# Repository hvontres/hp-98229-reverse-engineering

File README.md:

# hp 98229 Memory Module reverse engineering
This is an attempt at documenting the HP 98229 Memory module used in the HP 9000 375/380/385 models.

It comes in 2mb, 4mb 8mb and 16mb sizes. The 4mb size seems to exist in two flavors: the older version using 36 256K x 4 memory chips and a newer version using 9 1M x 4 chips.

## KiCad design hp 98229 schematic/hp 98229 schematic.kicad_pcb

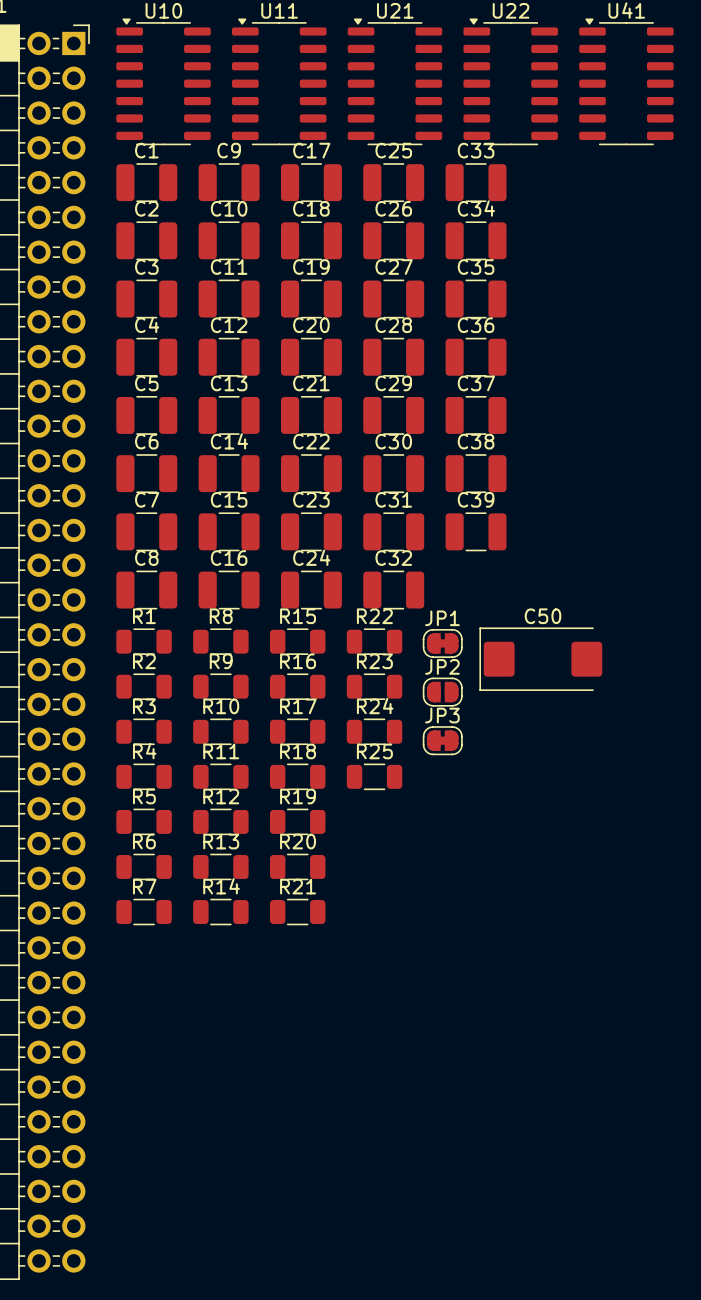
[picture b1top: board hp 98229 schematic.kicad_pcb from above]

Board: 2 copper layers, 74 parts (0 on the bottom side), 51 nets, no tracks yet.

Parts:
C1, C2, C3, C4, C5, C6, C7, C8, C9, C10, C11, C12, C13, C14, C15, C16, C17, C18, C19, C20, C21, C22, C23, C24, C25, C26, C27, C28, C29, C30, C31, C32, C33, C34, C35, C36, C37, C38, C39: 0.1 uF; C_1210_3225Metric_Pad1.33x2.70mm_HandSolder
C50: 47 uF; CP_EIA-7343-20_Kemet-V_Pad2.25x2.55mm_HandSolder
J1: Conn_02x36_Top_Bottom; PinSocket_2x36_P2.54mm_Horizontal
JP1: Jumper_2_Bridged; SolderJumper-2_P1.3mm_Bridged_RoundedPad1.0x1.5mm
JP2: Jumper_2_Open; SolderJumper-2_P1.3mm_Open_RoundedPad1.0x1.5mm
JP3: Jumper_2_closed; SolderJumper-2_P1.3mm_Bridged_RoundedPad1.0x1.5mm
R1, R2, R3, R4, R5, R6, R7, R8, R9, R10, R11, R12, R13, R14, R15, R16, R17, R18, R19, R20, R21, R22, R23, R24, R25: 15; R_1206_3216Metric
U10, U11, U21, U22, U41: 74AHCT04; SOIC-14_3.9x8.7mm_P1.27mm

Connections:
/CAS0: J1.18, U10.9
/CAS1: J1.55, U21.9
/CAS2: J1.15, U41.1
/CAS3: J1.50, U41.3
/ID0: J1.24, JP1.2 (B)
/ID1: J1.23, JP2.1 (A)
/ID2: J1.61, JP3.2 (B)
/OE: J1.17, U21.13, U41.5
/RAS: J1.53, U11.5, U22.5, U41.9, U41.13
/WRITE0: J1.52, U11.11
/WRITE1: J1.20, U21.5
/WRITE2: J1.56, U11.9
/WRITE3: J1.14, U21.11
/WRITE4: J1.49, U21.1
/~A0: J1.22, U10.5
/~A1: J1.60, U22.9
/~A2: J1.21, U22.13
/~A3: J1.59, U22.11
/~A4: J1.12, U11.1
/~A5: J1.58, U11.13
/~A6: J1.11, U10.13
/~A7: J1.48, U10.1
/~A8: J1.10, U22.1
/~A9: J1.47, U10.3
GND: C1.1, C2.1, C3.1, C4.1, C5.1, C6.1, C7.1, C8.1, C9.1, C10.1, C11.1, C12.1, C13.1, C14.1, C15.1, C16.1, C17.1, C18.1, C19.1, C20.1, C21.1, C22.1, C23.1, C24.1, C25.1, C26.1, C27.1, C28.1, C29.1, C30.1, C31.1, C32.1, C33.1, C34.1, C35.1, C36.1, C37.1, C38.1, C39.1, C50.2, J1.13, J1.16, J1.27, J1.36, J1.37, J1.46, J1.54, J1.57, JP1.1 (A), JP2.2 (B), JP3.1 (A), U10.7 (GND), U11.7 (GND), U21.7 (GND), U22.7 (GND), U41.7 (GND)
unnamed: R1.2, U10.4
unnamed: R2.2, U10.2
unnamed: R3.2, U21.2
unnamed: R4.2, U41.4
unnamed: R5.2, U11.10
unnamed: R6.2, U21.8
unnamed: R7.2, U11.8
unnamed: R8.2, U11.12
unnamed: R9.2, U22.10
unnamed: R10.2, U22.8
unnamed: R11.2, U11.6
unnamed: R12.2, U22.6
unnamed: R13.2, U41.8
unnamed: R14.2, U41.12
unnamed: R15.1, U22.2
unnamed: R16.1, U10.12
unnamed: R17.1, U11.2
unnamed: R18.1, U21.10
unnamed: R19.1, U41.2
unnamed: R20.1, U10.8
unnamed: R21.1, U21.6
unnamed: R22.1, U22.12
unnamed: R23.1, U10.6
unnamed: R24.1, U41.6
unnamed: R25.1, U21.12
VCC: C1.2, C2.2, C3.2, C4.2, C5.2, C6.2, C7.2, C8.2, C9.2, C10.2, C11.2, C12.2, C13.2, C14.2, C15.2, C16.2, C17.2, C18.2, C19.2, C20.2, C21.2, C22.2, C23.2, C24.2, C25.2, C26.2, C27.2, C28.2, C29.2, C30.2, C31.2, C32.2, C33.2, C34.2, C35.2, C36.2, C37.2, C38.2, C39.2, C50.1, J1.5, J1.19, J1.51, J1.68, U10.11, U10.14 (VCC), U11.3, U11.14 (VCC), U21.3, U21.14 (VCC), U22.3, U22.14 (VCC), U41.11, U41.14 (VCC)

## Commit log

2025-04-02 Initial version of Kicad Schematic
2025-04-02 First draft of readme file
2025-04-02 move pdf schematic to top directory
2025-04-04 fix C0D3 label on connector
2025-06-01 Add table to show id jumper configurations
